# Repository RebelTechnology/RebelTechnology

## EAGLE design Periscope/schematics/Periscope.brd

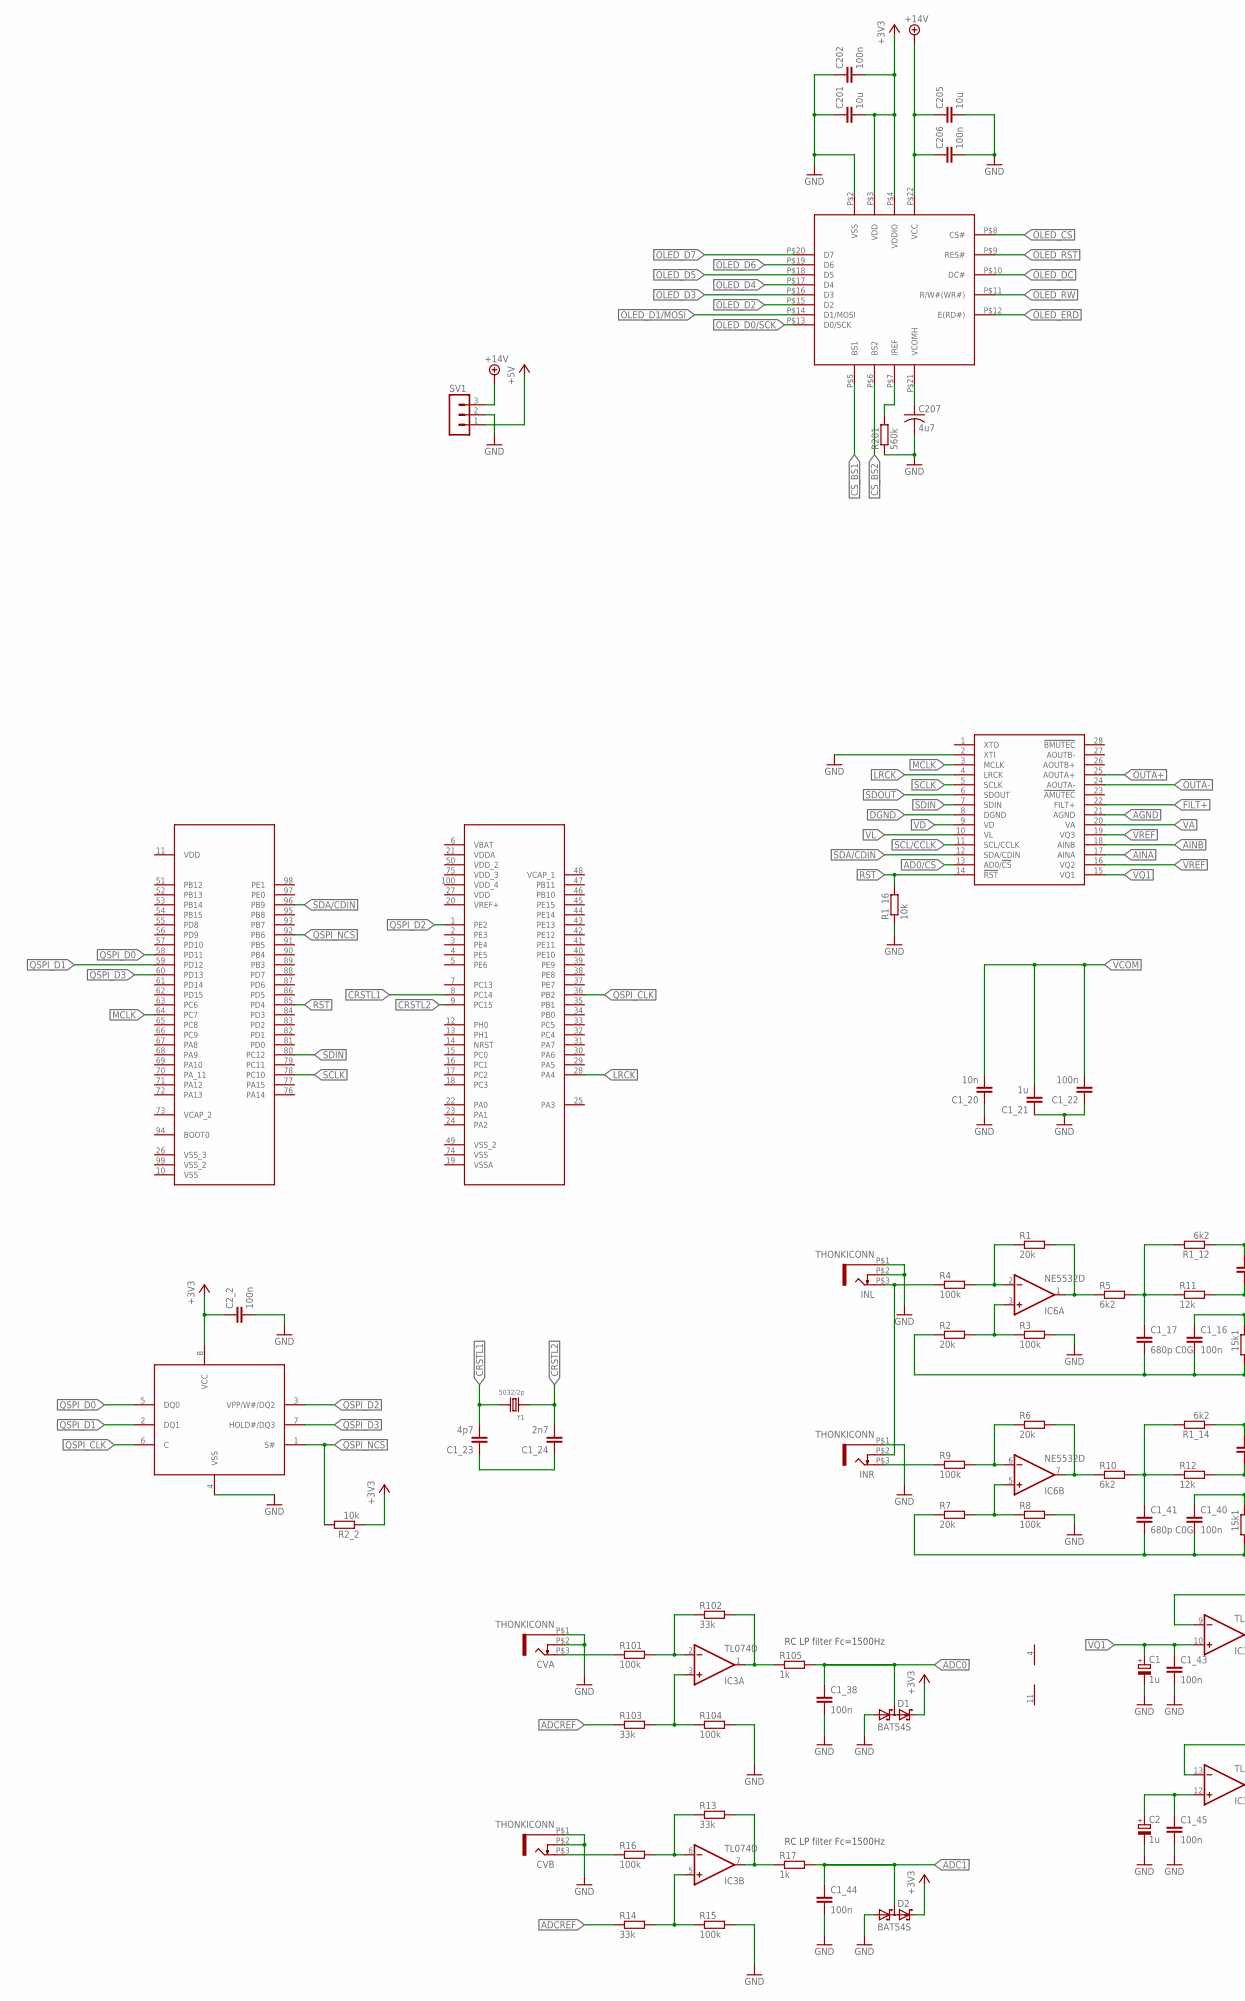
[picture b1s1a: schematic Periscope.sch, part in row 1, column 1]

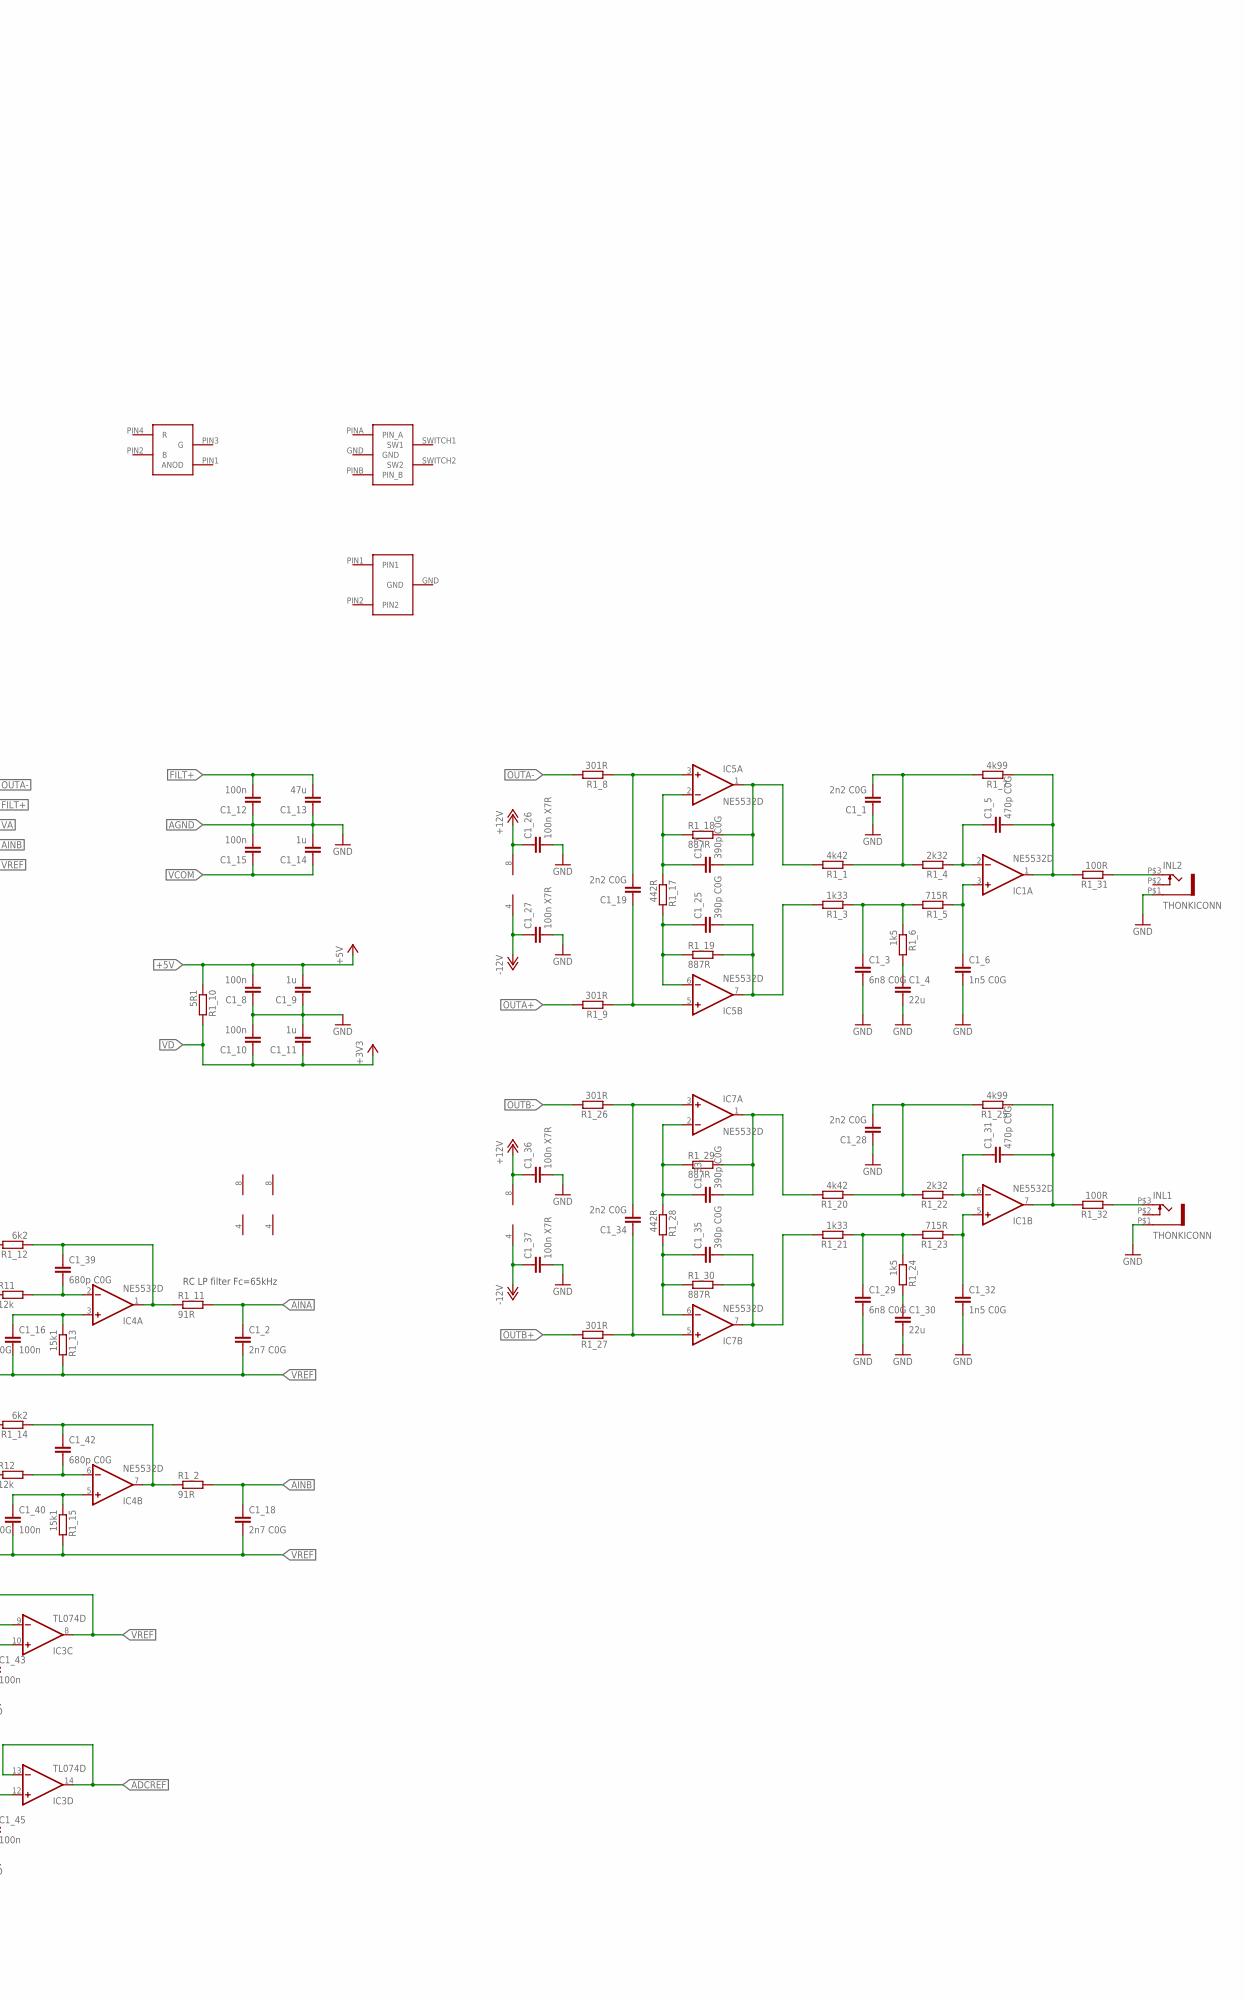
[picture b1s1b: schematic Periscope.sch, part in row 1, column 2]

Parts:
C1, C2: 1u; 153CLV-0505
C1_1, C1_19, C1_28, C1_34: 2n2 C0G; C0603
C1_2, C1_18: 2n7 C0G; C0603
C1_3, C1_29: 6n8 C0G; C0603
C1_4, C1_30: 22u; C0603
C1_5, C1_31: 470p C0G; C0603
C1_6, C1_32: 1n5 C0G; C0603
C1_7, C1_25, C1_33, C1_35: 390p C0G; C0603
C1_8, C1_10, C1_12, C1_15, C1_16, C1_22, C1_38, C1_40, C1_43, C1_44, C1_45, C2_2, C202, C206: 100n; C0603
C1_9, C1_11, C1_14, C1_21: 1u; C0603
C1_13: 47u; C0603
C1_17, C1_39, C1_41, C1_42: 680p C0G; C0603
C1_20: 10n; C0603
C1_23: 4p7; C0603
C1_24: 2n7; C0603
C1_26, C1_27, C1_36, C1_37: 100n X7R; C0603
C201, C205: 10u; C0603
C207: 4u7; C0603
CVA: THONKICONN
CVB: THONKICONN
D1, D2: BAT54S; SOT23
IC1, IC4, IC5, IC6, IC7: NE5532D; SO08
IC3: TL074D; SO14
INL, INL1, INL2: THONKICONN
INR: THONKICONN
R1, R2, R6, R7: 20k; R0603
R1_1, R1_20: 4k42; R0603
R1_2, R1_11: 91R; R0603
R1_3, R1_21: 1k33; R0603
R1_4, R1_22: 2k32; R0603
R1_5, R1_23: 715R; R0603
R1_6, R1_24: 1k5; R0603
R1_7, R1_25: 4k99; R0603
R1_8, R1_9, R1_26, R1_27: 301R; R0603
R1_10: 5R1; R0603
R1_12, R1_14, R5, R10: 6k2; R0603
R1_13, R1_15: 15k1; R0603
R1_16, R2_2: 10k; R0603
R1_17, R1_28: 442R; R0603
R1_18, R1_19, R1_29, R1_30: 887R; R0603
R1_31, R1_32: 100R; R0603
R3, R4, R8, R9, R15, R16, R101, R104: 100k; R0603
R11, R12: 12k; R0603
R13, R14, R102, R103: 33k; R0603
R17, R105: 1k; R0603
R201: 560k; R0603
SV1: MA03-1
U$1: PLCC4_RGB_LED
U$2: EC12E2424407
U$3: MCOT096064AZ-RGBM
U$4: CS4271; TSSOP28-0.65-9.7X4.4MM
U$5: STM32F746VGT6; QFP50P1600X1600X160-100N
U$6: N25Q128A13; SO8W
U$8: EC12E2430802
Y1: 5032/2p; X2-SMD-5.0X3.2X1.3MM

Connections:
+3V3: C2_2.1, C201.2, C202.2, D1.2 (C2), D2.2 (C2), R2_2.1, U$3.P$3 (VDD), U$3.P$4 (VDDIO), U$6.8 (VCC)
+5V: C1_8.2, C1_9.2, R1_10.1, SV1.1
+12V: C1_26.1, C1_36.1, IC5.8 (V+), IC7.8 (V+)
+14V: C205.1, C206.1, SV1.3, U$3.P$22 (VCC)
-12V: C1_27.1, C1_37.1, IC5.4 (V-), IC7.4 (V-)
AD0/CS: U$4.13 (AD0/!CS)
ADC0: C1_38.1, D1.3 (C1A2), R105.2
ADC1: C1_44.1, D2.3 (C1A2), R17.2
ADCREF: IC3.13 (-IN), IC3.14 (OUT), R14.1, R103.1
AGND: C1_12.1, C1_13.1, C1_14.2, C1_15.2, U$4.21 (AGND)
AINA: C1_2.1, R1_11.2, U$4.17 (AINA)
AINB: C1_18.1, R1_2.2, U$4.18 (AINB)
ANALOG_OUTA: C1_5.2, IC1.1 (OUT), R1_7.1, R1_31.2
ANALOG_OUTB: C1_31.2, IC1.7 (OUT), R1_25.1, R1_32.2
CRSTL1: C1_23.2, U$5.8 (PC14), Y1.2
CRSTL2: C1_24.2, U$5.9 (PC15), Y1.1
CS_BS1: U$3.P$5 (BS1)
CS_BS2: U$3.P$6 (BS2)
DGND: U$4.8 (DGND)
FILT+: C1_12.2, C1_13.2, U$4.22 (FILT+)
GND: C1.-, C1_1.1, C1_3.2, C1_4.2, C1_6.2, C1_8.1, C1_9.1, C1_10.2, C1_11.2, C1_20.1, C1_21.1, C1_22.1, C1_26.2, C1_27.2, C1_28.1, C1_29.2, C1_30.2, C1_32.2, C1_36.2, C1_37.2, C1_38.2, C1_43.2, C1_44.2, C1_45.2, C2.-, C2_2.2, C201.1, C202.1, C205.2, C206.2, C207.2, CVA.P$1 (5), CVA.P$2 (4), CVB.P$1 (5), CVB.P$2 (4), D1.1 (A1), D2.1 (A1), INL.P$1 (5), INL.P$2 (4), INL1.P$1 (5), INL2.P$1 (5), INR.P$1 (5), R1_16.1, R3.2, R8.2, R15.2, R104.2, R201.1, SV1.2, U$3.P$2 (VSS), U$4.2 (XTI), U$6.4 (VSS)
LRCK: U$4.4 (LRCK), U$5.28 (PA4)
MCLK: U$4.3 (MCLK), U$5.64 (PC7)
unnamed: C1_3.1, R1_3.1, R1_5.2, R1_6.1
unnamed: IC3.3 (+IN), R103.2, R104.1
unnamed: C1_23.1, C1_24.1
unnamed: IC3.2 (-IN), R101.2, R102.1
unnamed: IC3.1 (OUT), R102.2, R105.1
unnamed: C207.1, U$3.P$21 (VCOMH)
unnamed: CVA.P$3 (3), R101.1
unnamed: R201.2, U$3.P$7 (IREF)
unnamed: C1_4.1, R1_6.2
unnamed: C1_1.2, R1_1.1, R1_4.2, R1_7.2
unnamed: C1_7.2, IC5.1 (OUT), R1_1.2, R1_18.2
unnamed: C1_25.2, IC5.7 (OUT), R1_3.2, R1_19.2
unnamed: C1_5.1, IC1.2 (-IN), R1_4.1
unnamed: C1_6.1, IC1.3 (+IN), R1_5.1
unnamed: C1_19.2, IC5.3 (+IN), R1_8.1
unnamed: C1_17.1, R1_12.2, R5.2, R11.1
unnamed: C1_7.1, IC5.2 (-IN), R1_17.1, R1_18.1
unnamed: C1_39.2, IC4.2 (-IN), R11.2
unnamed: C1_39.1, IC4.1 (OUT), R1_11.1, R1_12.1
unnamed: C1_19.1, IC5.5 (+IN), R1_9.1
unnamed: C1_16.1, IC4.3 (+IN), R1_13.1
unnamed: C1_25.1, IC5.6 (-IN), R1_17.2, R1_19.1
unnamed: INL2.P$3 (3), R1_31.1
unnamed: INL1.P$3 (3), R1_32.1
unnamed: C1_29.1, R1_21.1, R1_23.2, R1_24.1
unnamed: C1_28.2, R1_20.1, R1_22.2, R1_25.2
unnamed: C1_31.1, IC1.6 (-IN), R1_22.1
unnamed: C1_32.1, IC1.5 (+IN), R1_23.1
unnamed: C1_30.1, R1_24.2
unnamed: C1_33.2, IC7.1 (OUT), R1_20.2, R1_29.2
unnamed: C1_35.2, IC7.7 (OUT), R1_21.2, R1_30.2
unnamed: C1_34.2, IC7.3 (+IN), R1_26.1
unnamed: C1_33.1, IC7.2 (-IN), R1_28.1, R1_29.1
unnamed: C1_34.1, IC7.5 (+IN), R1_27.1
unnamed: C1_35.1, IC7.6 (-IN), R1_28.2, R1_30.1
unnamed: IC6.3 (+IN), R2.2, R3.1
unnamed: C1_42.1, IC4.7 (OUT), R1_2.1, R1_14.1
unnamed: IC6.2 (-IN), R1.1, R4.2
unnamed: INL.P$3 (3), INR.P$2 (4), R4.1
unnamed: IC6.1 (OUT), R1.2, R5.1
unnamed: C1_41.1, R1_14.2, R10.2, R12.1
unnamed: IC6.5 (+IN), R7.2, R8.1
unnamed: IC6.6 (-IN), R6.1, R9.2
unnamed: INR.P$3 (3), R9.1
unnamed: IC6.7 (OUT), R6.2, R10.1
unnamed: C1_42.2, IC4.6 (-IN), R12.2
unnamed: C1_40.1, IC4.5 (+IN), R1_15.1
unnamed: C1_45.1, C2.+, IC3.12 (+IN)
unnamed: IC3.5 (+IN), R14.2, R15.1
unnamed: IC3.6 (-IN), R13.1, R16.2
unnamed: CVB.P$3 (3), R16.1
unnamed: IC3.7 (OUT), R13.2, R17.1
OLED_CS: U$3.P$8 (CS#)
OLED_D0/SCK: U$3.P$13 (D0/SCK)
OLED_D1/MOSI: U$3.P$14 (D1/MOSI)
OLED_D2: U$3.P$15 (D2)
OLED_D3: U$3.P$16 (D3)
OLED_D4: U$3.P$17 (D4)
OLED_D5: U$3.P$18 (D5)
OLED_D6: U$3.P$19 (D6)
OLED_D7: U$3.P$20 (D7)
OLED_DC: U$3.P$10 (DC#)
OLED_ERD: U$3.P$12 (E(RD#))
OLED_RST: U$3.P$9 (RES#)
OLED_RW: U$3.P$11 (R/W#(WR#))
OUTA+: R1_9.2, U$4.25 (AOUTA+)
OUTA-: R1_8.2, U$4.24 (AOUTA-)
OUTB+: R1_27.2
OUTB-: R1_26.2
QSPI_CLK: U$5.36 (PB2), U$6.6 (C)
QSPI_D0: U$5.58 (PD11), U$6.5 (DQ0)
QSPI_D1: U$5.59 (PD12), U$6.2 (DQ1)
QSPI_D2: U$5.1 (PE2), U$6.3 (VPP/W#/DQ2)
QSPI_D3: U$5.60 (PD13), U$6.7 (HOLD#/DQ3)
QSPI_NCS: R2_2.2, U$5.92 (PB6), U$6.1 (S#)
RST: R1_16.2, U$4.14 (!RST), U$5.85 (PD4)
SCL/CCLK: U$4.11 (SCL/CCLK)
SCLK: U$4.5 (SCLK), U$5.78 (PC10)
SDA/CDIN: U$4.12 (SDA/CDIN), U$5.96 (PB9)
SDIN: U$4.7 (SDIN), U$5.80 (PC12)
SDOUT: U$4.6 (SDOUT)
V+: IC1.8 (V+), IC3.4 (V+), IC4.8 (V+), IC6.8 (V+)
V-: IC1.4 (V-), IC3.11 (V-), IC4.4 (V-), IC6.4 (V-)
VA: U$4.20 (VA)
VCOM: C1_14.1, C1_15.1, C1_20.2, C1_21.2, C1_22.2
VD: C1_10.1, C1_11.1, R1_10.2, U$4.9 (VD)
VL: U$4.10 (VL)
VQ1: C1.+, C1_43.1, IC3.10 (+IN), U$4.15 (VQ1)
VREF: C1_2.2, C1_16.2, C1_17.2, C1_18.2, C1_40.2, C1_41.2, IC3.8 (OUT), IC3.9 (-IN), R1_13.2, R1_15.2, R2.1, R7.1, U$4.16 (VQ2), U$4.19 (VQ3)

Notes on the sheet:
RC LP filter Fc=1500Hz
RC LP filter Fc=65kHz

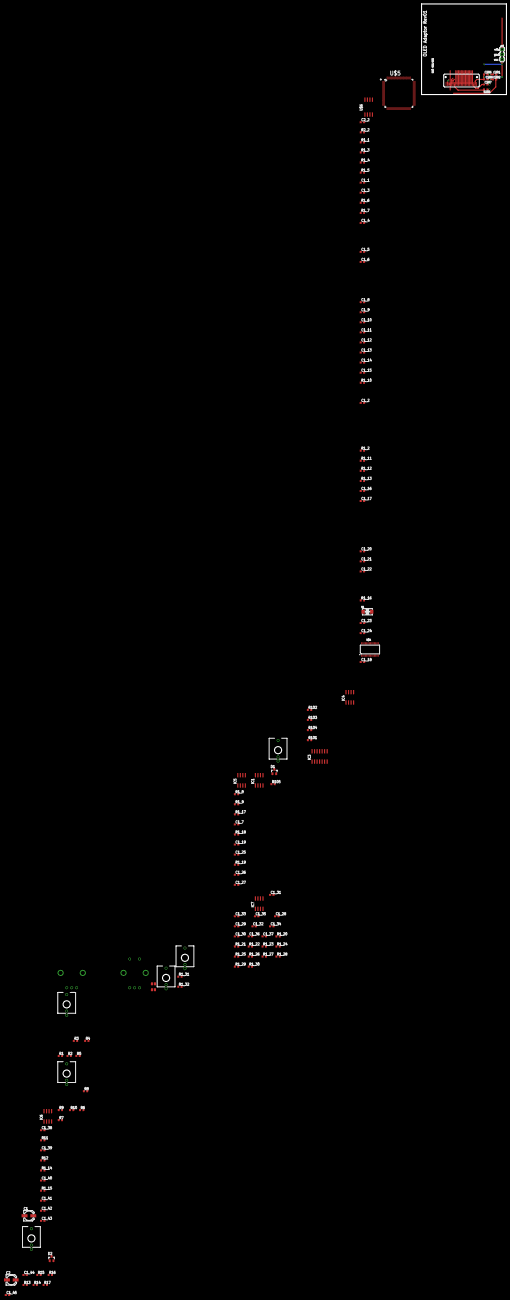
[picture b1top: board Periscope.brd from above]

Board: 2 copper layers, 42.9 x 45.7 mm, 132 parts (0 on the bottom side), 89 nets.

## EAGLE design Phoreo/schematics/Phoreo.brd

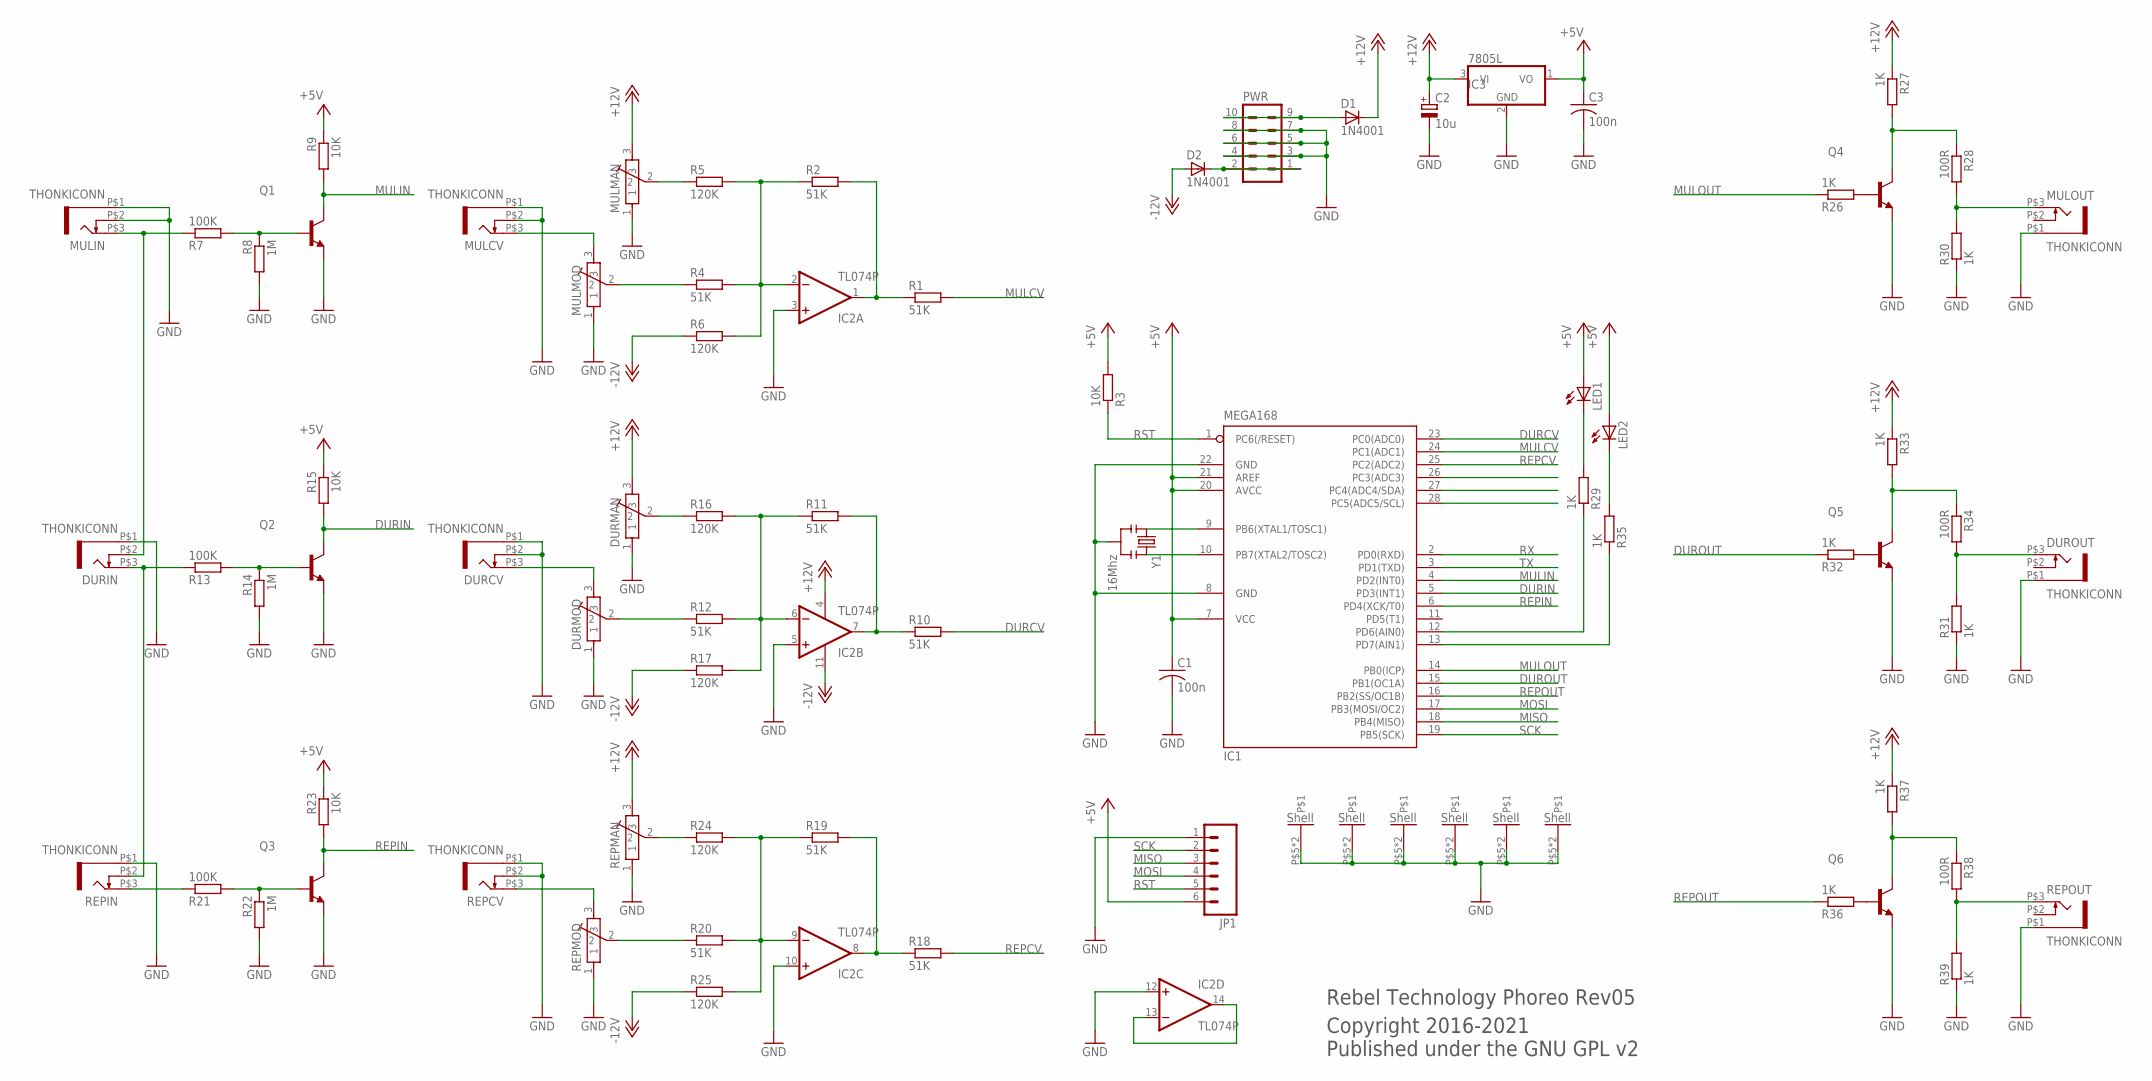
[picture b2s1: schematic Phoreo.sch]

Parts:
C1, C3: 100n; C050-024X044
C2: 10u; E5-6
D1, D2: 1N4001; DIODE-1N4001
DURCV: THONKICONN
DURIN: THONKICONN
DURMAN: POT-ALPS-RK09L1140
DURMOD: POT-ALPS-RK09L1140
DUROUT: THONKICONN
IC1: MEGA168; DIL28-3
IC2: TL074P; DIL14
IC3: 7805L; TO92
JP1: M06SIP; 1X06
LED1, LED2: LED3MM
MULCV: THONKICONN
MULIN: THONKICONN
MULMAN: POT-ALPS-RK09L1140
MULMOD: POT-ALPS-RK09L1140
MULOUT: THONKICONN
PWR: MA05-2
Q1, Q2, Q3, Q4, Q5, Q6: 2N3904-NPN-TO92-EBC; TO92-EBC
R1, R2, R4, R10, R11, R12, R18, R19, R20: 51K; 0204/7
R3, R9, R15, R23: 10K; 0204/7
R5, R6, R16, R17, R24, R25: 120K; 0204/7
R7, R13, R21: 100K; 0204/7
R8, R14, R22: 1M; 0204/7
R26, R27, R29, R30, R31, R32, R33, R35, R36, R37, R39: 1K; 0204/7
R28, R34, R38: 100R; 0204/7
REPCV: THONKICONN
REPIN: THONKICONN
REPMAN: POT-ALPS-RK09L1140
REPMOD: POT-ALPS-RK09L1140
REPOUT: THONKICONN
Y1: 16Mhz; RESONATOR-PTH

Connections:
+5V: C1.1, C3.1, IC1.7 (VCC), IC1.20 (AVCC), IC1.21 (AREF), IC3.1 (VO), JP1.6, LED1.A, LED2.A, R3.2, R9.1, R15.1, R23.1
+12V: C2.+, D1.C, DURMAN.3, IC2.4 (V+), IC3.3 (VI), MULMAN.3, R27.1, R33.1, R37.1, REPMAN.3
-12V: D2.A, IC2.11 (V-), R6.1, R17.1, R25.1
DURCV: IC1.23 (PC0(ADC0)), R10.2
DURIN: IC1.5 (PD3(INT1)), Q2.C, R15.2
DUROUT: IC1.15 (PB1(OC1A)), R32.1
DURSW: DURIN.P$2 (4), MULIN.P$3 (3), R7.1
GND: C1.2, C2.-, C3.2, DURCV.P$1 (5), DURCV.P$2 (4), DURIN.P$1 (5), DURMAN.1, DURMAN.P$5, DURMAN.P$6, DURMOD.1, DURMOD.P$5, DURMOD.P$6, DUROUT.P$1 (5), IC1.8 (GND), IC1.22 (GND), IC2.3 (+IN), IC2.5 (+IN), IC2.10 (+IN), IC2.12 (+IN), IC3.2 (GND), JP1.1, MULCV.P$1 (5), MULCV.P$2 (4), MULIN.P$1 (5), MULIN.P$2 (4), MULMAN.1, MULMAN.P$5, MULMAN.P$6, MULMOD.1, MULMOD.P$5, MULMOD.P$6, MULOUT.P$1 (5), PWR.3, PWR.4, PWR.5, PWR.6, PWR.7, PWR.8, Q1.E, Q2.E, Q3.E, Q4.E, Q5.E, Q6.E, R8.2, R14.2, R22.2, R30.1, R31.1, R39.1, REPCV.P$1 (5), REPCV.P$2 (4), REPIN.P$1 (5), REPMAN.1, REPMAN.P$5, REPMAN.P$6, REPMOD.1, REPMOD.P$5, REPMOD.P$6, REPOUT.P$1 (5), Y1.2
MISO: IC1.18 (PB4(MISO)), JP1.3
MOSI: IC1.17 (PB3(MOSI/OC2)), JP1.4
MULCV: IC1.24 (PC1(ADC1)), R1.2
MULIN: IC1.4 (PD2(INT0)), Q1.C, R9.2
MULOUT: IC1.14 (PB0(ICP)), R26.1
unnamed: DURCV.P$3 (3), DURMOD.3
unnamed: IC2.6 (-IN), R11.1, R12.2, R16.2, R17.2
unnamed: DURMAN.2, R16.1
unnamed: IC2.7 (OUT), R10.1, R11.2
unnamed: DURMOD.2, R12.1
unnamed: IC2.9 (-IN), R19.1, R20.2, R24.2, R25.2
unnamed: R24.1, REPMAN.2
unnamed: IC2.8 (OUT), R18.1, R19.2
unnamed: R20.1, REPMOD.2
unnamed: IC2.13 (-IN), IC2.14 (OUT)
unnamed: REPCV.P$3 (3), REPMOD.3
unnamed: IC2.2 (-IN), R2.1, R4.2, R5.2, R6.2
unnamed: MULMAN.2, R5.1
unnamed: IC2.1 (OUT), R1.1, R2.2
unnamed: MULMOD.2, R4.1
unnamed: IC1.9 (PB6(XTAL1/TOSC1)), Y1.1
unnamed: IC1.10 (PB7(XTAL2/TOSC2)), Y1.3
unnamed: MULCV.P$3 (3), MULMOD.3
unnamed: LED1.K (C), R29.2
unnamed: LED2.K (C), R35.2
unnamed: IC1.13 (PD7(AIN1)), R35.1
unnamed: Q5.B, R32.2
unnamed: Q1.B, R7.2, R8.1
unnamed: MULOUT.P$3 (3), R28.2, R30.2
unnamed: IC1.12 (PD6(AIN0)), R29.1
unnamed: DUROUT.P$3 (3), R31.2, R34.2
unnamed: Q2.B, R13.2, R14.1
unnamed: Q5.C, R33.2, R34.1
unnamed: Q4.B, R26.2
unnamed: Q6.B, R36.2
unnamed: R38.2, R39.2, REPOUT.P$3 (3)
unnamed: DURIN.P$3 (3), R13.1, REPIN.P$2 (4)
unnamed: Q4.C, R27.2, R28.1
unnamed: Q6.C, R37.2, R38.1
unnamed: Q3.B, R21.2, R22.1
unnamed: D1.A, PWR.9, PWR.10
unnamed: R21.1, REPIN.P$3 (3)
unnamed: D2.C, PWR.1, PWR.2
REPCV: IC1.25 (PC2(ADC2)), R18.2
REPIN: IC1.6 (PD4(XCK/T0)), Q3.C, R23.2
REPOUT: IC1.16 (PB2(SS/OC1B)), R36.1
RST: IC1.1 (PC6(/RESET)), JP1.5, R3.1
RX: IC1.2 (PD0(RXD))
SCK: IC1.19 (PB5(SCK)), JP1.2
TX: IC1.3 (PD1(TXD))

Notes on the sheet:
Rebel Technology Phoreo Rev05
Copyright 2016-2021 Published under the GNU GPL v2

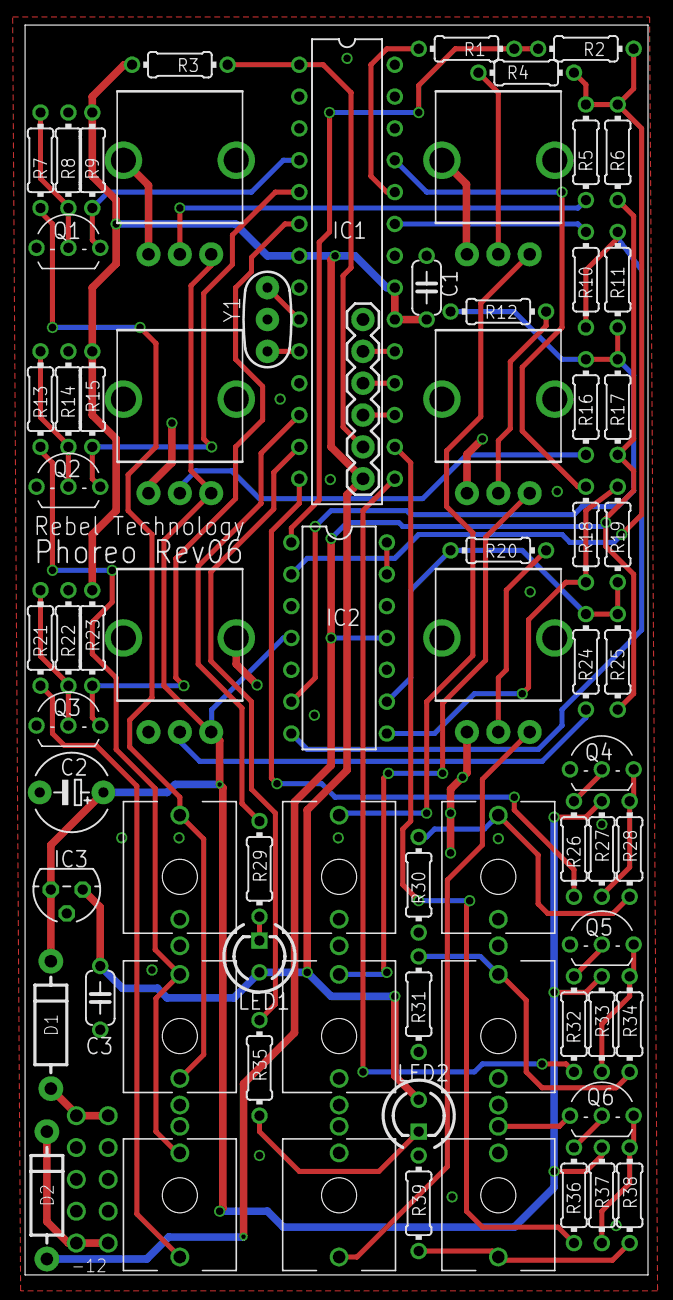
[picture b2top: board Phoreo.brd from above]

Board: 2 copper layers, 49.7 x 99.7 mm, 73 parts (1 on the bottom side), 56 nets.

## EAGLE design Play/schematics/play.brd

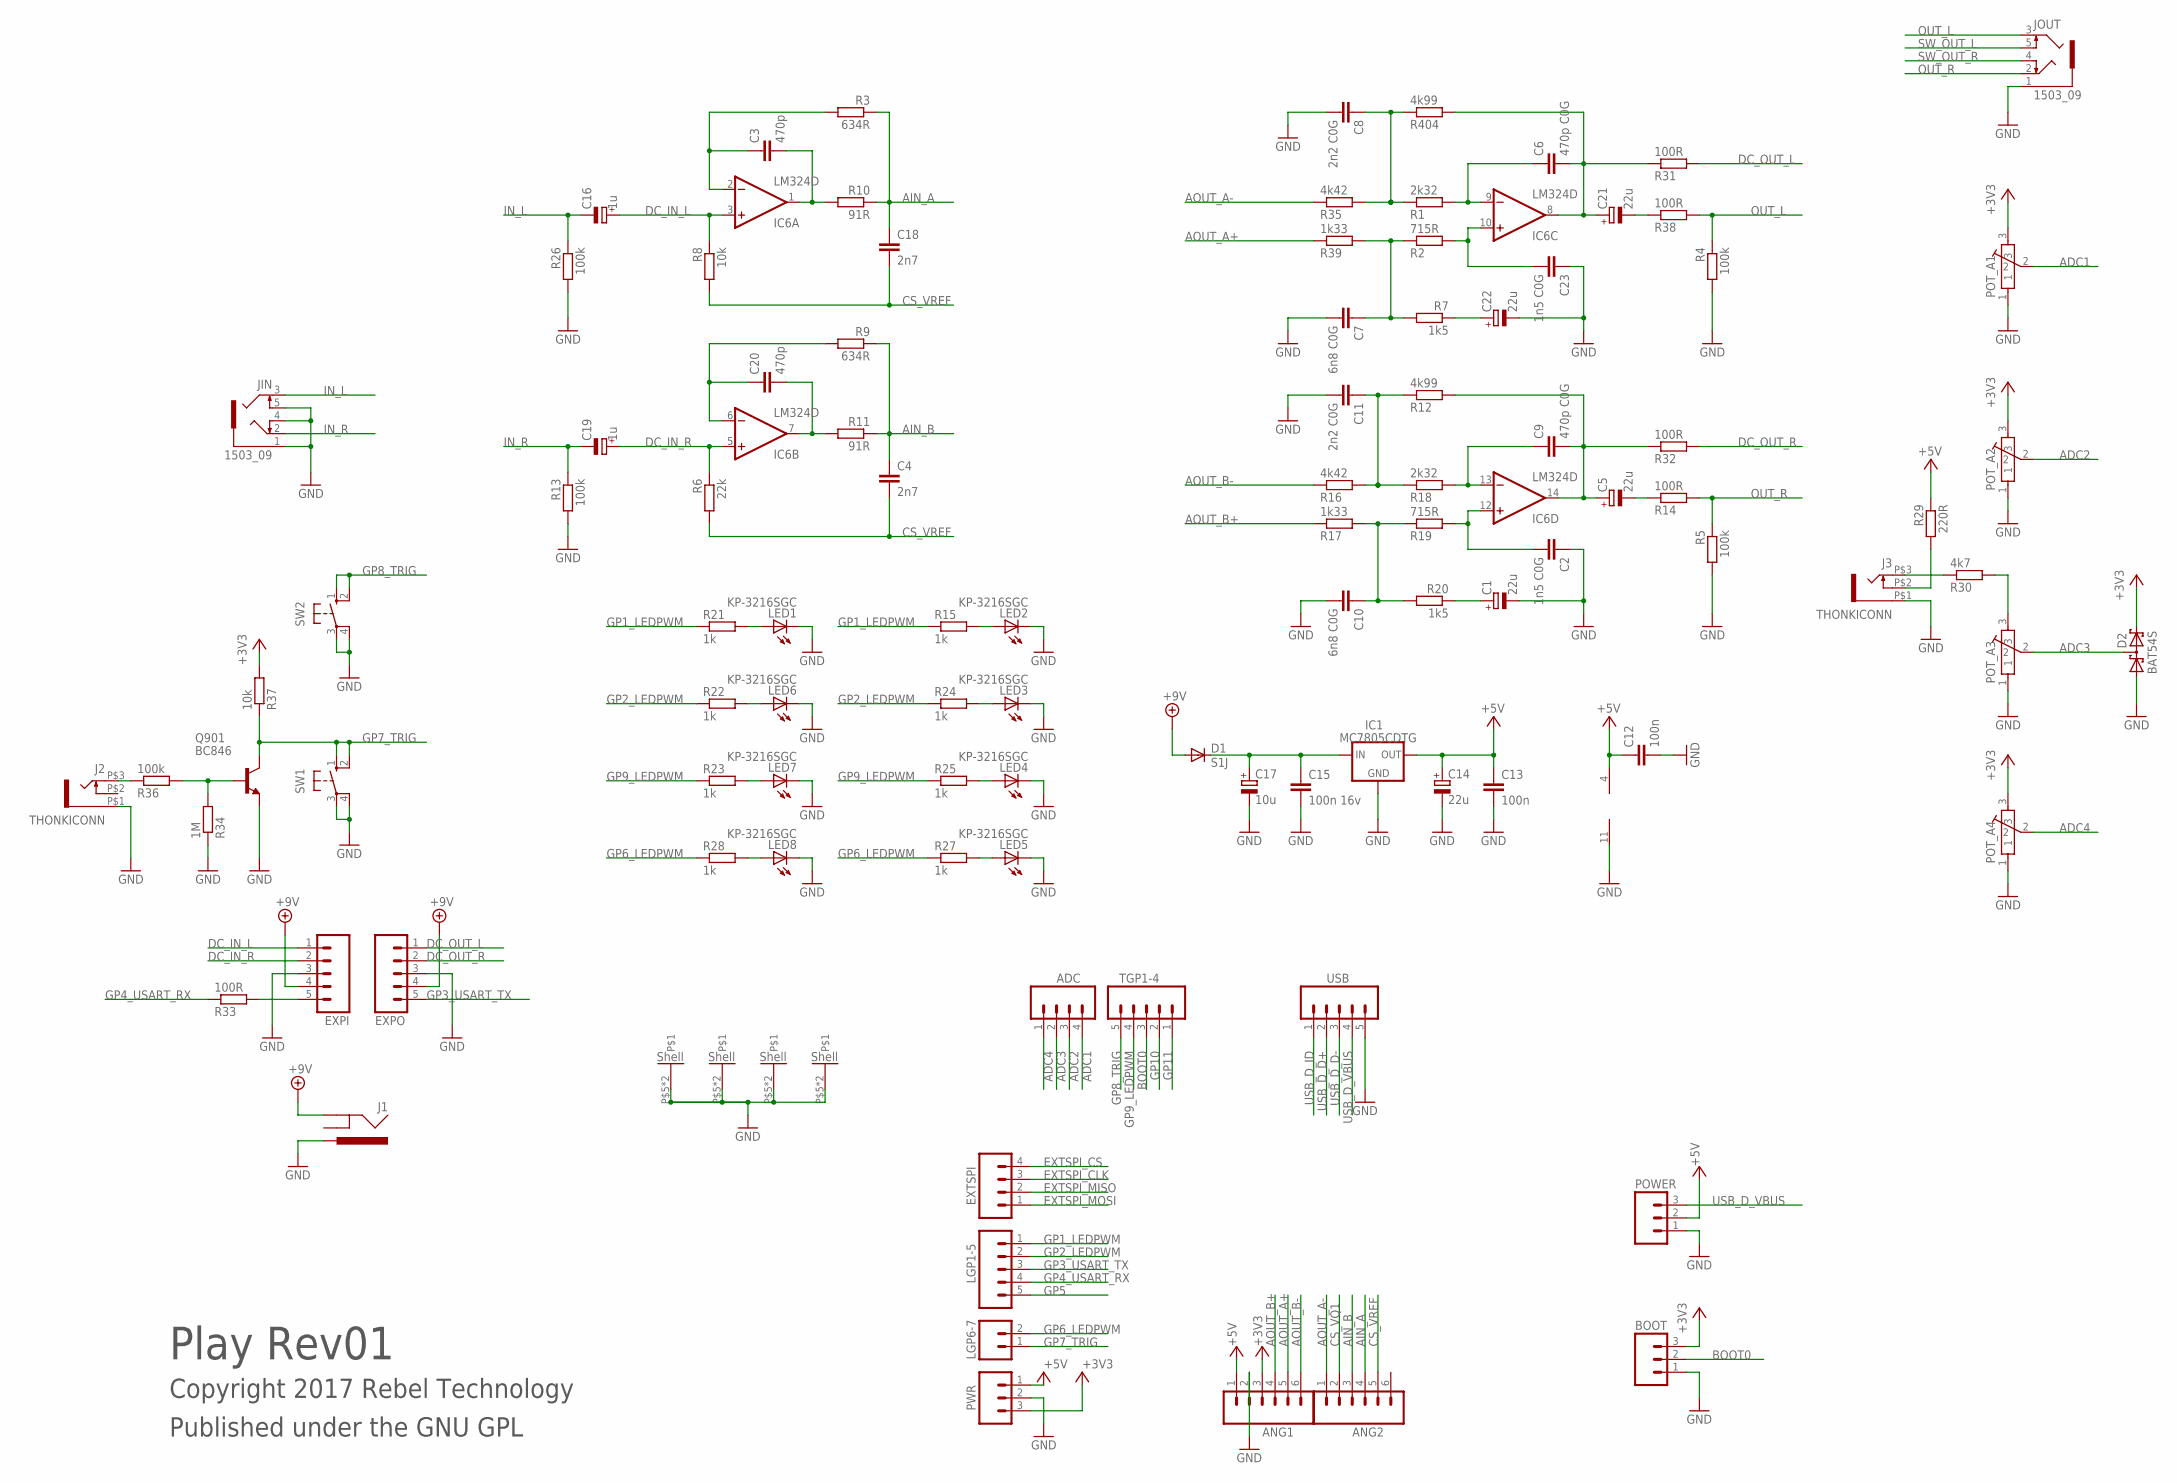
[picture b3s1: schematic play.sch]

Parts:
ADC: M04PTH; 1X04
ANG1, ANG2: M06SIP; 1X06
BOOT: M03PTH; 1X03
C1, C5, C14, C21, C22: 22u; CPOL-5
C2, C23: 1n5 C0G; C0603
C3, C20: 470p; C0603
C4, C18: 2n7; C0603
C6, C9: 470p C0G; C0603
C7, C10: 6n8 C0G; C0603
C8, C11: 2n2 C0G; C0603
C12, C13: 100n; C0603
C15: 100n 16v; C0603
C16, C19: 1u; 153CLV-0405
C17: 10u; 153CLV-0405
D1: S1J; SMA-DIODE
D2: BAT54S; SOT23
EXPI: M05PTH; 1X05
EXPO: M05PTH; 1X05
EXTSPI: M04PTH; 1X04
IC1: MC7805CDTG; DPACK
IC6: LM324D; SO14
J1: POWER_JACKPTH; POWER_JACK_PTH
J2, J3: THONKICONN
JIN: 1503_09
JOUT: 1503_09
LED1, LED2, LED3, LED4, LED5, LED6, LED7, LED8: KP-3216SGC; LED-1206; FARNELL 853-0033
LGP1-5: M05PTH; 1X05
LGP6-7: M02PTH; 1X02
POT_A1, POT_A2, POT_A3, POT_A4: POT-ALPS-RK09L1140
POWER: M03PTH; 1X03
PWR: M03PTH; 1X03
Q901: BC846; SOT23
R1, R18: 2k32; 0603
R2, R19: 715R; 0603
R3, R9: 634R; 0603
R4, R5, R13, R26, R36: 100k; 0603
R6: 22k; 0603
R7, R20: 1k5; 0603
R8, R37: 10k; 0603
R10, R11: 91R; 0603
R12, R404: 4k99; 0603
R14, R31, R32, R33, R38: 100R; 0603
R15, R21, R22, R23, R24, R25, R27, R28: 1k; 0603
R16, R35: 4k42; 0603
R17, R39: 1k33; 0603
R29: 220R; 0603
R30: 4k7; 0603
R34: 1M; 0603
SW1, SW2: 10-XX; B3F-10XX
TGP1-4: M05PTH; 1X05
USB: M05PTH; 1X05

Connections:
+3V3: ANG1.3, BOOT.3, D2.2 (C2), POT_A1.3, POT_A2.3, POT_A4.3, PWR.3, R37.2
+5V: ANG1.1, C12.1, C13.1, C14.+, IC1.3 (OUT), IC6.4 (V+), POWER.2, PWR.1, R29.1
+9V: D1.A, EXPI.4, EXPO.4, J1.GND
ADC1: ADC.4, POT_A1.2
ADC2: ADC.3, POT_A2.2
ADC3: ADC.2, D2.3 (C1A2), POT_A3.2
ADC4: ADC.1, POT_A4.2
AIN_A: ANG2.4, C18.1, R3.1, R10.1
AIN_B: ANG2.3, C4.1, R9.1, R11.1
AOUT_A+: ANG1.5, R39.1
AOUT_A-: ANG2.1, R35.1
AOUT_B+: ANG1.4, R17.1
AOUT_B-: ANG1.6, R16.1
BOOT0: BOOT.2, TGP1-4.3
CS_VQ1: ANG2.2
CS_VREF: ANG2.5, C4.2, C18.2, R6.2, R8.2
DC_IN_L: C16.+, EXPI.1, IC6.3 (+IN), R8.1
DC_IN_R: C19.+, EXPI.2, IC6.5 (+IN), R6.1
DC_OUT_L: EXPO.1, R31.2
DC_OUT_R: EXPO.2, R32.2
EXTSPI_CLK: EXTSPI.3
EXTSPI_CS: EXTSPI.4
EXTSPI_MISO: EXTSPI.2
EXTSPI_MOSI: EXTSPI.1
GND: ANG1.2, BOOT.1, C1.-, C2.1, C7.2, C8.2, C10.2, C11.2, C12.2, C13.2, C14.-, C15.2, C17.-, C22.-, C23.1, D2.1 (A1), EXPI.3, EXPO.3, IC1.4 (GND), IC6.11 (V-), J1.PWR, J2.P$1 (5), J3.P$1 (5), JIN.1, JIN.4, JIN.5, JOUT.1, LED1.C, LED2.C, LED3.C, LED4.C, LED5.C, LED6.C, LED7.C, LED8.C, POT_A1.1, POT_A1.P$5, POT_A1.P$6, POT_A2.1, POT_A2.P$5, POT_A2.P$6, POT_A3.1, POT_A3.P$5, POT_A3.P$6, POT_A4.1, POT_A4.P$5, POT_A4.P$6, POWER.1, PWR.2, Q901.2 (E), R4.2, R5.2, R13.2, R26.2, R34.1, SW1.3, SW1.4 (P1), SW2.3, SW2.4 (P1), USB.5
GP1_LEDPWM: LGP1-5.1, R15.1, R21.1
GP2_LEDPWM: LGP1-5.2, R22.1, R24.1
GP3_USART_TX: EXPO.5, LGP1-5.3
GP4_USART_RX: LGP1-5.4, R33.1
GP5: LGP1-5.5
GP6_LEDPWM: LGP6-7.2, R27.1, R28.1
GP7_TRIG: LGP6-7.1, Q901.3 (C), R37.1, SW1.1 (S), SW1.2 (S1)
GP8_TRIG: SW2.1 (S), SW2.2 (S1), TGP1-4.5
GP9_LEDPWM: R23.1, R25.1, TGP1-4.4
GP10: TGP1-4.2
GP11: TGP1-4.1
IN_L: C16.-, JIN.3, R26.1
IN_R: C19.-, JIN.2, R13.1
unnamed: EXPI.5, R33.2
unnamed: C3.1, IC6.2 (-IN), R3.2
unnamed: C20.2, IC6.7 (OUT), R11.2
unnamed: C20.1, IC6.6 (-IN), R9.2
unnamed: C3.2, IC6.1 (OUT), R10.2
unnamed: C6.1, IC6.9 (-IN), R1.2
unnamed: C1.+, R20.1
unnamed: C21.-, R38.1
unnamed: C22.+, R7.1
unnamed: C23.2, IC6.10 (+IN), R2.2
unnamed: C5.+, C9.2, IC6.14 (OUT), R12.2, R32.1
unnamed: C5.-, R14.1
unnamed: LED2.A, R15.2
unnamed: C7.1, R2.1, R7.2, R39.2
unnamed: LED1.A, R21.2
unnamed: LED6.A, R22.2
unnamed: LED7.A, R23.2
unnamed: LED8.A, R28.2
unnamed: LED3.A, R24.2
unnamed: LED4.A, R25.2
unnamed: J2.P$3 (3), R36.1
unnamed: J3.P$2 (4), R29.2
unnamed: C11.1, R12.1, R16.2, R18.1
unnamed: POT_A3.3, R30.2
unnamed: C9.1, IC6.13 (-IN), R18.2
unnamed: J3.P$3 (3), R30.1
unnamed: LED5.A, R27.2
unnamed: C15.1, C17.+, D1.C, IC1.1 (IN)
unnamed: C2.2, IC6.12 (+IN), R19.2
unnamed: C10.1, R17.2, R19.1, R20.2
unnamed: Q901.1 (B), R34.2, R36.2
unnamed: C6.2, C21.+, IC6.8 (OUT), R31.1, R404.2
unnamed: C8.1, R1.1, R35.2, R404.1
OUT_L: JOUT.3, R4.1, R38.2
OUT_R: JOUT.2, R5.1, R14.2
SW_OUT_L: JOUT.5
SW_OUT_R: JOUT.4
USB_D_D+: USB.2
USB_D_D-: USB.3
USB_D_ID: USB.1
USB_D_VBUS: POWER.3, USB.4

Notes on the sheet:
Play Rev01
Copyright 2017 Rebel Technology
Published under the GNU GPL

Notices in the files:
parts and their libraries:
SparkFun: Licensing: CC v3.0 Share-Alike You are welcome to use this library for commercial purposes.
